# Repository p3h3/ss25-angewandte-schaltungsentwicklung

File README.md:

# ss25-angewandte-schaltungsentwicklung
Ich will 4 CP

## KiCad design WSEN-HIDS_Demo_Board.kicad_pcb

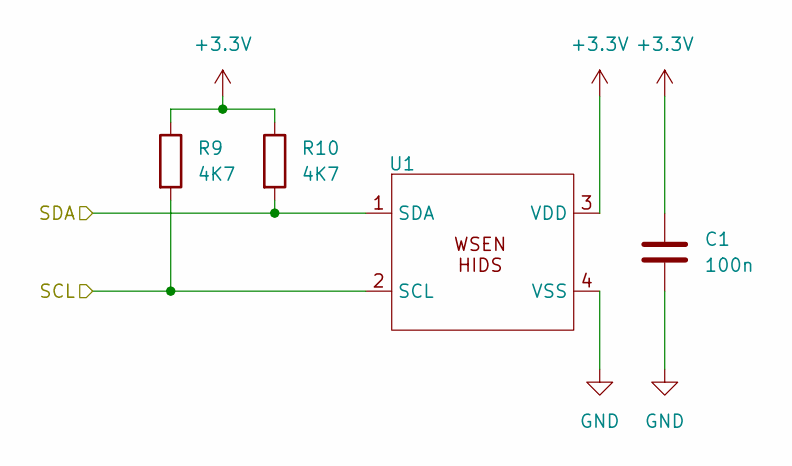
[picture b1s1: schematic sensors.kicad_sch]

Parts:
C1: 100n; C_0603_1608Metric; MPN 100n 50V X5R
R9, R10: 4K7; R_0603_1608Metric
U1: WSEN-HIDS_Footprint; MPN 2525020210002

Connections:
+3.3V: C1.1, R9.1, R10.1, U1.3 (VDD); also elsewhere on the board
/Raspberry Pi Pico/SCL: R9.2, U1.2 (SCL); also elsewhere on the board
/Raspberry Pi Pico/SDA: R10.2, U1.1 (SDA); also elsewhere on the board
GND: C1.2, U1.4 (VSS); also elsewhere on the board

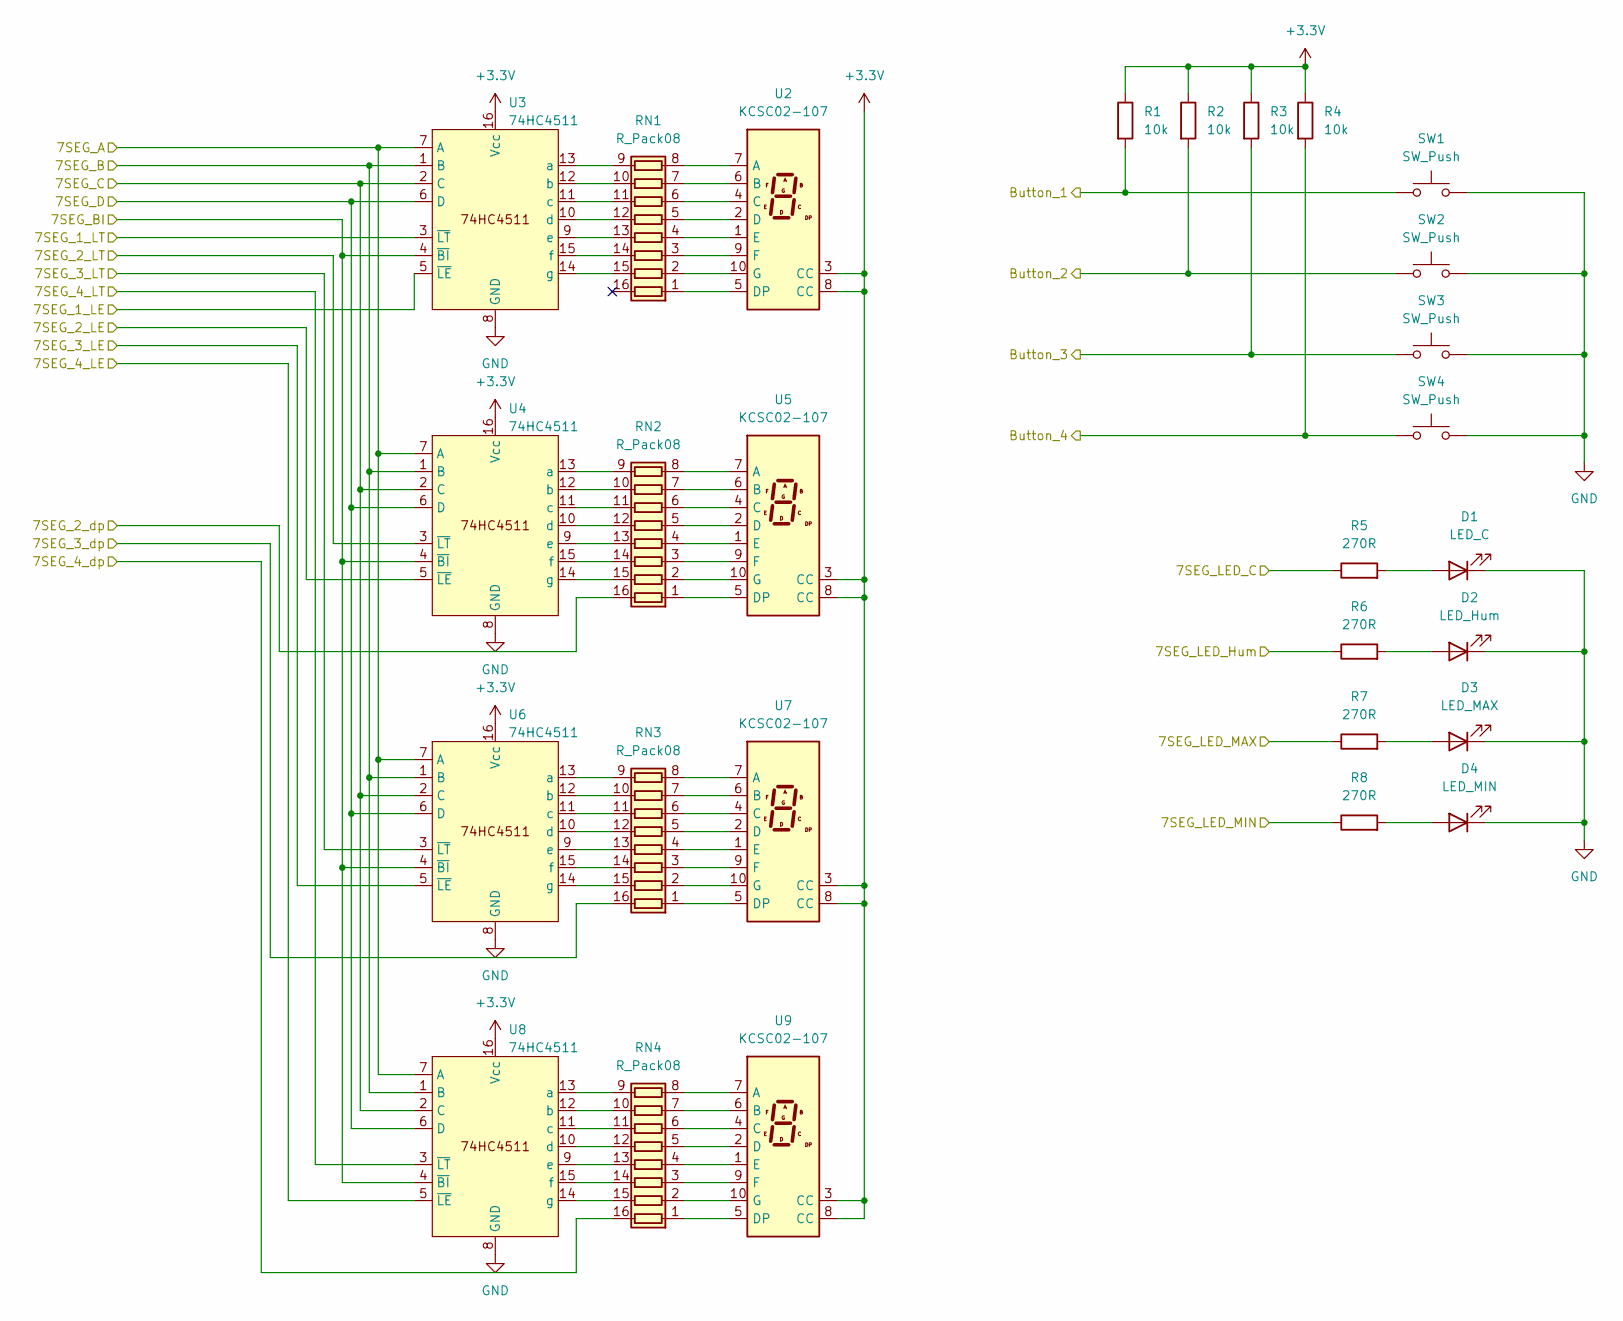
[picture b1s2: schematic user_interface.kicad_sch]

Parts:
D1: LED_C; LED_0603_1608Metric
D2: LED_Hum; LED_0603_1608Metric
D3: LED_MAX; LED_0603_1608Metric
D4: LED_MIN; LED_0603_1608Metric
R1, R2, R3, R4: 10k; R_0603_1608Metric
R5, R6, R7, R8: 270R; R_0603_1608Metric
RN1, RN2, RN3, RN4: R_Pack08; R_Array_Convex_8x0602
SW1, SW2, SW3, SW4: SW_Push; SW_Push_1P1T_NO_Vertical_Wuerth_434133025816
U2, U5, U7, U9: KCSC02-107; 7SEGMENT-LED__HDSM531_HDSM533_SMD; MPN 157143S12700
U3, U4, U6, U8: 74HC4511; SO-16_3.9x9.9mm_P1.27mm; MPN 74HC4511

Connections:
+3.3V: R1.1, R2.1, R3.1, R4.1, U2.3 (CC), U2.8 (CC), U3.16 (Vcc), U4.16 (Vcc), U5.3 (CC), U5.8 (CC), U6.16 (Vcc), U7.3 (CC), U7.8 (CC), U8.16 (Vcc), U9.3 (CC), U9.8 (CC); also elsewhere on the board
/Raspberry Pi Pico/GPIO2: U3.3 (~LT); also elsewhere on the board
/Raspberry Pi Pico/GPIO3: U4.3 (~LT); also elsewhere on the board
/Raspberry Pi Pico/GPIO4: U6.3 (~LT); also elsewhere on the board
/Raspberry Pi Pico/GPIO5: U8.3 (~LT); also elsewhere on the board
/Raspberry Pi Pico/GPIO6: U3.7 (A), U4.7 (A), U6.7 (A), U8.7 (A); also elsewhere on the board
/Raspberry Pi Pico/GPIO7: U3.1 (B), U4.1 (B), U6.1 (B), U8.1 (B); also elsewhere on the board
/Raspberry Pi Pico/GPIO8: U3.2 (C), U4.2 (C), U6.2 (C), U8.2 (C); also elsewhere on the board
/Raspberry Pi Pico/GPIO9: U3.6 (D), U4.6 (D), U6.6 (D), U8.6 (D); also elsewhere on the board
/Raspberry Pi Pico/GPIO10: R1.2, SW1.1; also elsewhere on the board
/Raspberry Pi Pico/GPIO11: R2.2, SW2.1; also elsewhere on the board
/Raspberry Pi Pico/GPIO12: R3.2, SW3.1; also elsewhere on the board
/Raspberry Pi Pico/GPIO13: R4.2, SW4.1; also elsewhere on the board
/Raspberry Pi Pico/GPIO14: U4.5 (~LE); also elsewhere on the board
/Raspberry Pi Pico/GPIO15: U3.4 (~BI), U4.4 (~BI), U6.4 (~BI), U8.4 (~BI); also elsewhere on the board
/Raspberry Pi Pico/GPIO16: RN2.16 (R1.2); also elsewhere on the board
/Raspberry Pi Pico/GPIO17: U6.5 (~LE); also elsewhere on the board
/Raspberry Pi Pico/GPIO18: U3.5 (~LE); also elsewhere on the board
/Raspberry Pi Pico/GPIO19: R8.1; also elsewhere on the board
/Raspberry Pi Pico/GPIO20: R7.1; also elsewhere on the board
/Raspberry Pi Pico/GPIO21: U8.5 (~LE); also elsewhere on the board
/Raspberry Pi Pico/GPIO22: RN3.16 (R1.2); also elsewhere on the board
/Raspberry Pi Pico/GPIO26: R5.1; also elsewhere on the board
/Raspberry Pi Pico/GPIO27: RN4.16 (R1.2); also elsewhere on the board
/Raspberry Pi Pico/GPIO28: R6.1; also elsewhere on the board
GND: D1.1 (K), D2.1 (K), D3.1 (K), D4.1 (K), SW1.2, SW2.2, SW3.2, SW4.2, U3.8 (GND), U4.8 (GND), U6.8 (GND), U8.8 (GND); also elsewhere on the board
unnamed: D1.2 (A), R5.2
unnamed: D2.2 (A), R6.2
unnamed: D3.2 (A), R7.2
unnamed: D4.2 (A), R8.2
unnamed: RN1.1 (R1.1), U2.5 (DP)
unnamed: RN1.2 (R2.1), U2.10 (G)
unnamed: RN1.15 (R2.2), U3.14 (g)
unnamed: RN1.3 (R3.1), U2.9 (F)
unnamed: RN1.14 (R3.2), U3.15 (f)
unnamed: RN1.4 (R4.1), U2.1 (E)
unnamed: RN1.13 (R4.2), U3.9 (e)
unnamed: RN1.5 (R5.1), U2.2 (D)
unnamed: RN1.12 (R5.2), U3.10 (d)
unnamed: RN1.6 (R6.1), U2.4 (C)
unnamed: RN1.11 (R6.2), U3.11 (c)
unnamed: RN1.7 (R7.1), U2.6 (B)
unnamed: RN1.10 (R7.2), U3.12 (b)
unnamed: RN1.8 (R8.1), U2.7 (A)
unnamed: RN1.9 (R8.2), U3.13 (a)
unnamed: RN2.1 (R1.1), U5.5 (DP)
unnamed: RN2.2 (R2.1), U5.10 (G)
unnamed: RN2.15 (R2.2), U4.14 (g)
unnamed: RN2.3 (R3.1), U5.9 (F)
unnamed: RN2.14 (R3.2), U4.15 (f)
unnamed: RN2.4 (R4.1), U5.1 (E)
unnamed: RN2.13 (R4.2), U4.9 (e)
unnamed: RN2.5 (R5.1), U5.2 (D)
unnamed: RN2.12 (R5.2), U4.10 (d)
unnamed: RN2.6 (R6.1), U5.4 (C)
unnamed: RN2.11 (R6.2), U4.11 (c)
unnamed: RN2.7 (R7.1), U5.6 (B)
unnamed: RN2.10 (R7.2), U4.12 (b)
unnamed: RN2.8 (R8.1), U5.7 (A)
unnamed: RN2.9 (R8.2), U4.13 (a)
unnamed: RN3.1 (R1.1), U7.5 (DP)
unnamed: RN3.2 (R2.1), U7.10 (G)
unnamed: RN3.15 (R2.2), U6.14 (g)
unnamed: RN3.3 (R3.1), U7.9 (F)
unnamed: RN3.14 (R3.2), U6.15 (f)
unnamed: RN3.4 (R4.1), U7.1 (E)
unnamed: RN3.13 (R4.2), U6.9 (e)
unnamed: RN3.5 (R5.1), U7.2 (D)
unnamed: RN3.12 (R5.2), U6.10 (d)
unnamed: RN3.6 (R6.1), U7.4 (C)
unnamed: RN3.11 (R6.2), U6.11 (c)
unnamed: RN3.7 (R7.1), U7.6 (B)
unnamed: RN3.10 (R7.2), U6.12 (b)
unnamed: RN3.8 (R8.1), U7.7 (A)
unnamed: RN3.9 (R8.2), U6.13 (a)
unnamed: RN4.1 (R1.1), U9.5 (DP)
unnamed: RN4.2 (R2.1), U9.10 (G)
unnamed: RN4.15 (R2.2), U8.14 (g)
unnamed: RN4.3 (R3.1), U9.9 (F)
unnamed: RN4.14 (R3.2), U8.15 (f)
unnamed: RN4.4 (R4.1), U9.1 (E)
unnamed: RN4.13 (R4.2), U8.9 (e)
unnamed: RN4.5 (R5.1), U9.2 (D)
unnamed: RN4.12 (R5.2), U8.10 (d)
unnamed: RN4.6 (R6.1), U9.4 (C)
unnamed: RN4.11 (R6.2), U8.11 (c)
unnamed: RN4.7 (R7.1), U9.6 (B)
unnamed: RN4.10 (R7.2), U8.12 (b)
unnamed: RN4.8 (R8.1), U9.7 (A)
unnamed: RN4.9 (R8.2), U8.13 (a)

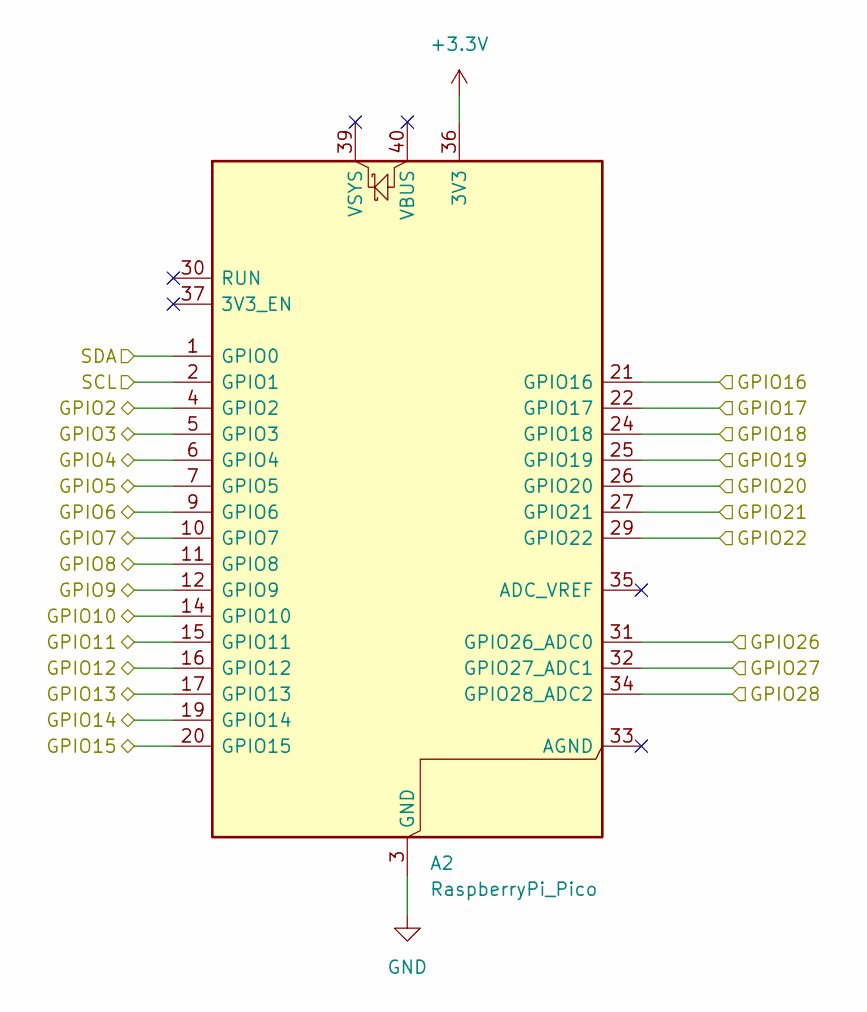
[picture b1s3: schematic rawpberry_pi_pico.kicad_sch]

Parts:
A2: RaspberryPi_Pico; RaspberryPi_Pico_Common_Unspecified

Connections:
+3.3V: A2.36 (3V3); also elsewhere on the board
/Raspberry Pi Pico/GPIO2: A2.4 (GPIO2); also elsewhere on the board
/Raspberry Pi Pico/GPIO3: A2.5 (GPIO3); also elsewhere on the board
/Raspberry Pi Pico/GPIO4: A2.6 (GPIO4); also elsewhere on the board
/Raspberry Pi Pico/GPIO5: A2.7 (GPIO5); also elsewhere on the board
/Raspberry Pi Pico/GPIO6: A2.9 (GPIO6); also elsewhere on the board
/Raspberry Pi Pico/GPIO7: A2.10 (GPIO7); also elsewhere on the board
/Raspberry Pi Pico/GPIO8: A2.11 (GPIO8); also elsewhere on the board
/Raspberry Pi Pico/GPIO9: A2.12 (GPIO9); also elsewhere on the board
/Raspberry Pi Pico/GPIO10: A2.14 (GPIO10); also elsewhere on the board
/Raspberry Pi Pico/GPIO11: A2.15 (GPIO11); also elsewhere on the board
/Raspberry Pi Pico/GPIO12: A2.16 (GPIO12); also elsewhere on the board
/Raspberry Pi Pico/GPIO13: A2.17 (GPIO13); also elsewhere on the board
/Raspberry Pi Pico/GPIO14: A2.19 (GPIO14); also elsewhere on the board
/Raspberry Pi Pico/GPIO15: A2.20 (GPIO15); also elsewhere on the board
/Raspberry Pi Pico/GPIO16: A2.21 (GPIO16); also elsewhere on the board
/Raspberry Pi Pico/GPIO17: A2.22 (GPIO17); also elsewhere on the board
/Raspberry Pi Pico/GPIO18: A2.24 (GPIO18); also elsewhere on the board
/Raspberry Pi Pico/GPIO19: A2.25 (GPIO19); also elsewhere on the board
/Raspberry Pi Pico/GPIO20: A2.26 (GPIO20); also elsewhere on the board
/Raspberry Pi Pico/GPIO21: A2.27 (GPIO21); also elsewhere on the board
/Raspberry Pi Pico/GPIO22: A2.29 (GPIO22); also elsewhere on the board
/Raspberry Pi Pico/GPIO26: A2.31 (GPIO26_ADC0); also elsewhere on the board
/Raspberry Pi Pico/GPIO27: A2.32 (GPIO27_ADC1); also elsewhere on the board
/Raspberry Pi Pico/GPIO28: A2.34 (GPIO28_ADC2); also elsewhere on the board
/Raspberry Pi Pico/SCL: A2.2 (GPIO1); also elsewhere on the board
/Raspberry Pi Pico/SDA: A2.1 (GPIO0); also elsewhere on the board
GND: A2.3 (GND), A2.8 (GND), A2.13 (GND), A2.18 (GND), A2.23 (GND), A2.28 (GND), A2.38 (GND); also elsewhere on the board

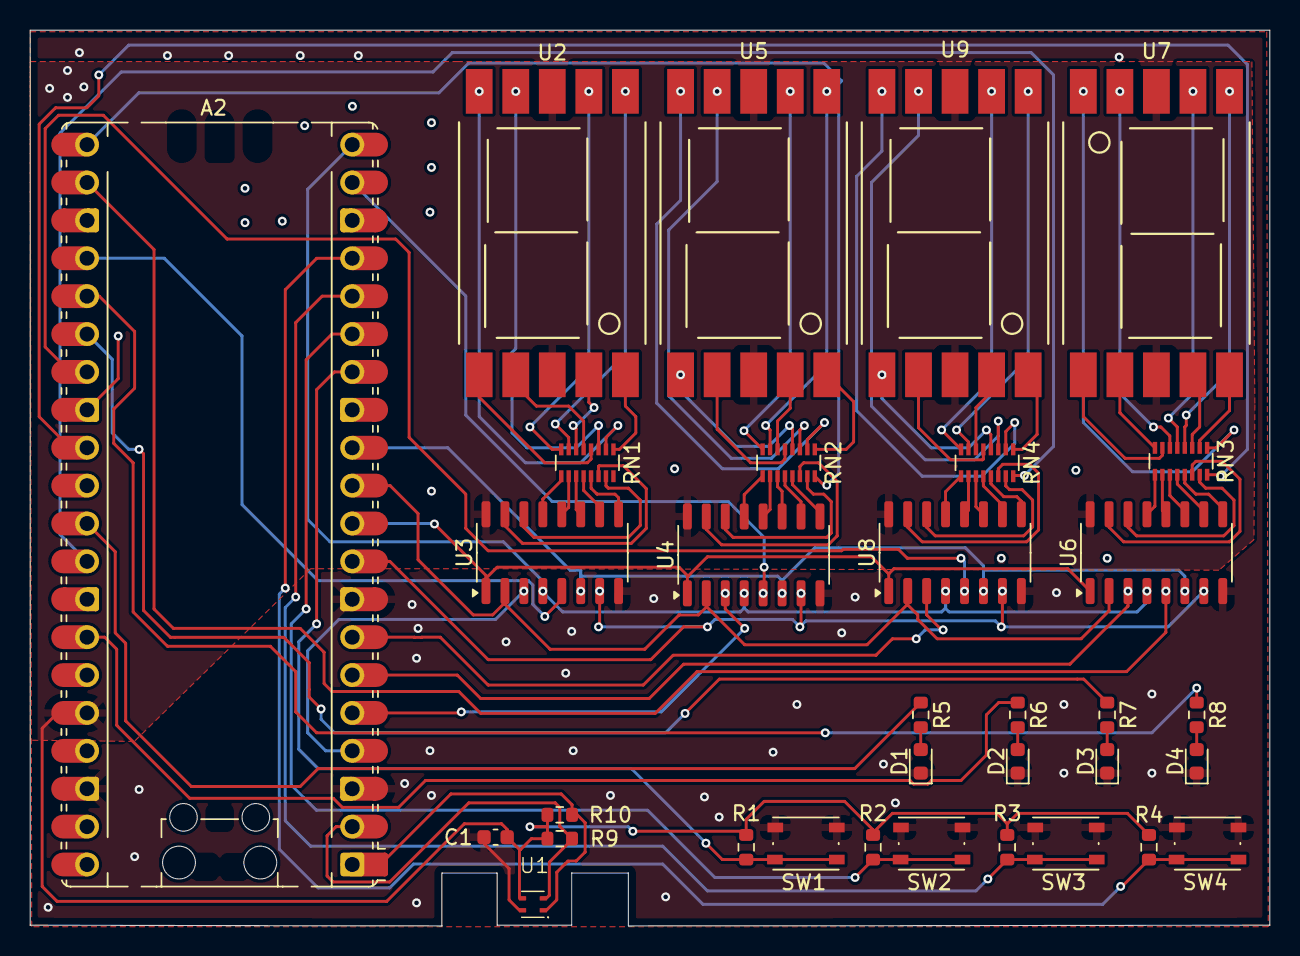
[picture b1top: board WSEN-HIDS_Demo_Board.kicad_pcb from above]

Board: 2 copper layers, 83.1 x 60.0 mm, 33 parts (0 on the bottom side), 92 nets.

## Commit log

2025-05-07 inital commit
    ICH WILL 5 CP
2025-06-25 unpack
2025-06-25 haha
